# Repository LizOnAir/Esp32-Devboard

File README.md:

# ESP32 Devboard

This devboard is created to learn about PCB design rules. I plan to use PCBA for this board.

## Features:
-  battery charging
-  2.4GHz wifi
-  bluetooth

## PCB
Here's my PCB! It was made in KiCad. 
### Schematic

### PCB

## BOM:
Here should be [everything](https://docs.google.com/spreadsheets/d/1wsxLwNynfaC6R5-2-ovum9rVKD0-UjsQx3AUx7Wjfbc/edit?usp=sharing) you need to make this:
- 1x PCBA

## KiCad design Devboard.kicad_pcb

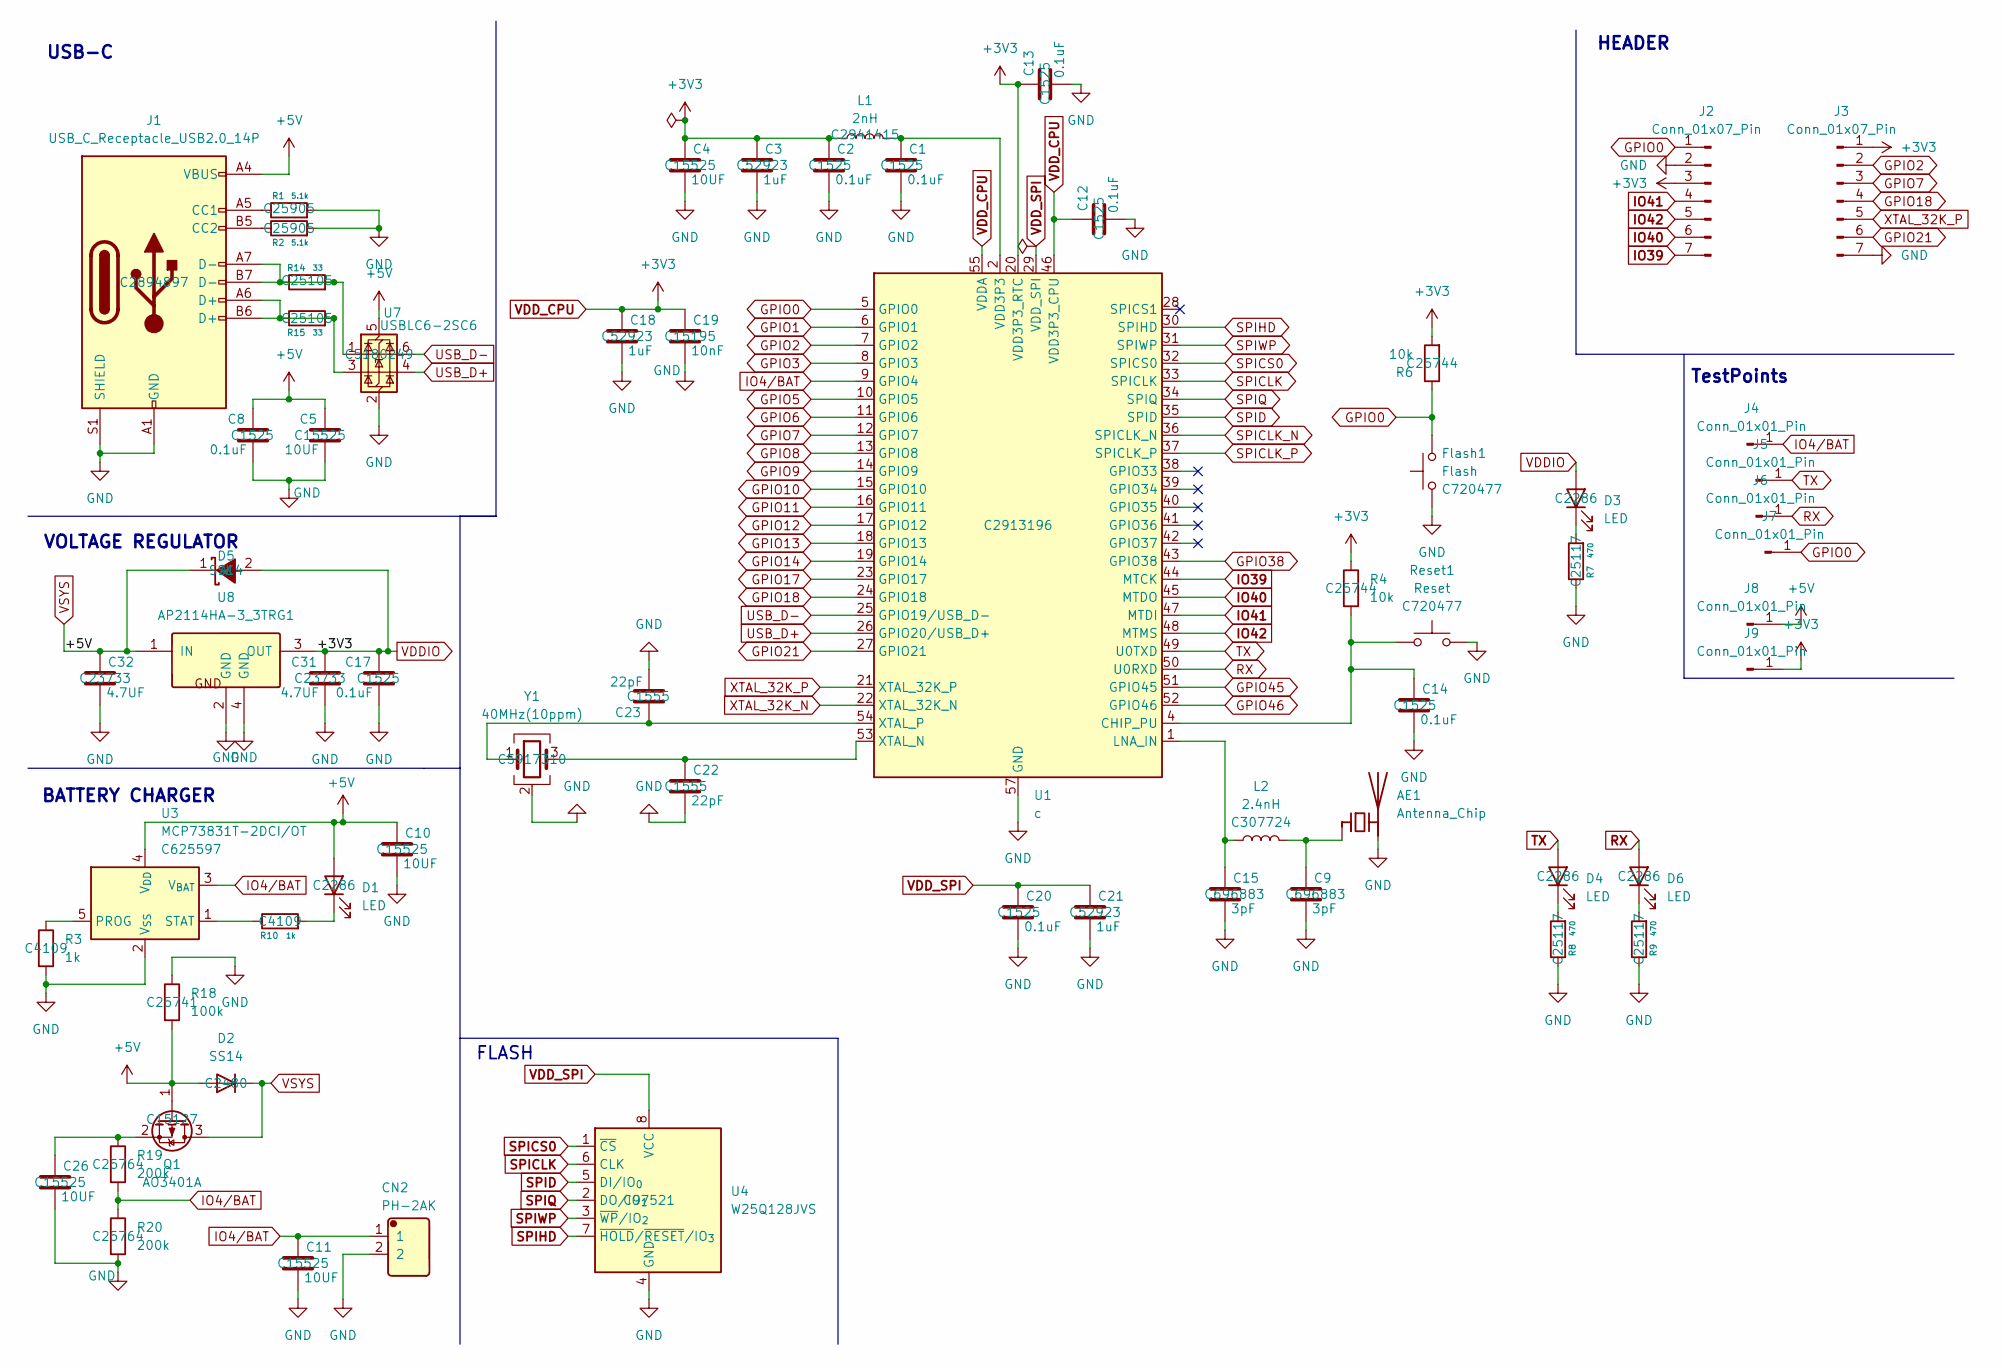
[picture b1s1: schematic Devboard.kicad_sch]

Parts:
AE1: Antenna_Chip; Texas_SWRA117D_2.4GHz_Left
C1, C2, C8, C12, C13, C14, C17, C20: 0.1uF; C_0402_1005Metric; MNF part num C1525
C3, C18, C21: 1uF; C_0402_1005Metric; MNF part num C52923
C4, C5, C10, C11, C26: 10UF; C_0402_1005Metric; MNF part num C15525
C9, C15: 3pF; C_0402_1005Metric; MNF part num C696883
C19: 10nF; C_0402_1005Metric; MNF part num C15195
C22, C23: 22pF; C_0402_1005Metric; MNF part num C1555
C31, C32: 4.7UF; C_0402_1005Metric; MNF part num C23733
CN2: PH-2AK; JST_PH_S2B-PH-K_1x02_P2.00mm_Horizontal; Manufacturer Part PH-2AK; LCSC C8886
D1, D3, D4, D6: LED; LED_0603_1608Metric; MNF part num C2286
D2: SS14; D_SMA; MNF part num C2480
D5: SS14; Manufacturer Part SS14; LCSC C2480
Flash1: Flash; SW_TS-1088-AR02016; MNF part num C720477
J1: USB_C_Receptacle_USB2.0_14P; USB_C_Receptacle_HCTL_HC-TYPE-C-16P-01A; MNF part num C2894897
J2, J3: Conn_01x07_Pin; PinHeader_1x07_P1.00mm_Vertical
J4, J5, J6, J7, J8, J9: Conn_01x01_Pin; TestPoint_Pad_D1.0mm
L1: 2nH; L_0402_1005Metric_Pad0.77x0.64mm_HandSolder; MNF part num C2941415
L2: 2.4nH; L_0402; MNF part num C307724
Q1: AO3401A; SOT-23; MNF part num C15127
R1, R2: 5.1k; R_0402; MNF part num C25905
R3, R10: 1k; R_0402; MNF part num C4109
R4, R6: 10k; R_0402_1005Metric; MNF part num C25744
R7, R8, R9: 470; R_0402; MNF part num C25117
R14, R15: 33; R_0402; MNF part num C25105
R18: 100k; R_0402; MNF part num C25741
R19, R20: 200k; R_0402; MNF part num C25764
Reset1: Reset; SW_TS-1088-AR02016; MNF part num C720477
U1: c; QFN-56-1EP_7x7mm_P0.4mm_EP4x4mm; MNF part num C2913196
U3: MCP73831T-2DCI/OT; SOT-23-5; MNF part num C625597
U4: W25Q128JVS; SOIC-8_5.3x5.3mm_P1.27mm; MNF part num C97521
U7: USBLC6-2SC6; SOT-23-6; MNF part num C5180249
U8: AP2114HA-3_3TRG1; Manufacturer Part AP2114HA-3.3TRG1; LCSC C460314
Y1: 40MHz(10ppm); Crystal_SMD_2520-4Pin_2.5x2.0mm; MNF part num C5917310

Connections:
GND: AE1.2 (PCB_Trace), C1.2, C2.2, C3.2, C4.2, C5.2, C8.2, C9.2, C10.2, C11.2, C12.2, C13.2, C14.2, C15.2, C17.2, C18.2, C19.2, C20.2, C21.2, C22.2, C23.2, C26.2, C31.2, C32.2, CN2.2, Flash1.1, J1.A1 (GND), J1.A12 (GND), J1.B1 (GND), J1.B12 (GND), J1.S1 (SHIELD), J2.2, J3.7, R1.2, R2.2, R3.2, R7.1, R8.1, R9.1, R18.1, R20.2, Reset1.2, U1.57 (GND), U3.2 (V_{SS}), U4.4 (GND), U7.2 (GND), U8.2 (GND), U8.4 (GND), Y1.2 (G), Y1.4 (G)
GPIO0: Flash1.2, J2.1, J7.1, R6.1, U1.5 (GPIO0)
GPIO1: U1.6 (GPIO1)
GPIO2: J3.2, U1.7 (GPIO2)
GPIO3: U1.8 (GPIO3)
GPIO5: U1.10 (GPIO5)
GPIO6: U1.11 (GPIO6)
GPIO7: J3.3, U1.12 (GPIO7)
GPIO8: U1.13 (GPIO8)
GPIO9: U1.14 (GPIO9)
GPIO10: U1.15 (GPIO10)
GPIO11: U1.16 (GPIO11)
GPIO12: U1.17 (GPIO12)
GPIO13: U1.18 (GPIO13)
GPIO14: U1.19 (GPIO14)
GPIO17: U1.23 (GPIO17)
GPIO18: J3.4, U1.24 (GPIO18)
GPIO21: J3.6, U1.27 (GPIO21)
GPIO38: U1.43 (GPIO38)
GPIO45: U1.51 (GPIO45)
GPIO46: U1.52 (GPIO46)
IO4/BAT: C11.1, CN2.1, J4.1, R19.2, R20.1, U1.9 (GPIO4), U3.3 (V_{BAT})
IO39: J2.7, U1.44 (MTCK)
IO40: J2.6, U1.45 (MTDO)
IO41: J2.4, U1.47 (MTDI)
IO42: J2.5, U1.48 (MTMS)
unnamed: AE1.1 (FEED), C9.1, L2.2
unnamed: C1.1, L1.2, U1.2 (VDD3P3), U1.3 (VDD3P3)
unnamed: D1.1 (K), R10.2
unnamed: D3.1 (K), R7.2
unnamed: D4.1 (K), R8.2
unnamed: D6.1 (K), R9.2
unnamed: J1.A5 (CC1), R1.1
unnamed: J1.B5 (CC2), R2.1
unnamed: J1.A6 (D+), J1.B6 (D+), R15.1, R15.2, U7.3 (I/O2)
unnamed: J1.A7 (D-), J1.B7 (D-), R14.1, R14.2, U7.1 (I/O1)
unnamed: C26.1, Q1.2 (S), R19.1
unnamed: C14.1, R4.2, Reset1.1, U1.4 (CHIP_PU)
unnamed: C15.1, L2.1, U1.1 (LNA_IN)
unnamed: C22.1, U1.53 (XTAL_N), Y1.3
unnamed: C23.1, U1.54 (XTAL_P), Y1.1
unnamed: R3.1, U3.5 (PROG)
unnamed: R10.1, U3.1 (STAT)
RX: D6.2 (A), J6.1, U1.50 (U0RXD)
SPICLK: U1.33 (SPICLK), U4.6 (CLK)
SPICLK_N: U1.36 (SPICLK_N)
SPICLK_P: U1.37 (SPICLK_P)
SPICS0: U1.32 (SPICS0), U4.1 (~CS)
SPID: U1.35 (SPID), U4.5 (DI/IO_{0})
SPIHD: U1.30 (SPIHD), U4.7 (~HOLD/~RESET/IO_{3})
SPIQ: U1.34 (SPIQ), U4.2 (DO/IO_{1})
SPIWP: U1.31 (SPIWP), U4.3 (~WP/IO_{2})
TX: D4.2 (A), J5.1, U1.49 (U0TXD)
USB_D+: U1.26 (GPIO20/USB_D+), U7.4 (I/O2)
USB_D-: U1.25 (GPIO19/USB_D-), U7.6 (I/O1)
VDDIO: C2.1, C3.1, C4.1, C12.1, C13.1, C17.1, C18.1, C19.1, C31.1, D3.2 (A), D5.2 (A), J2.3, J3.1, J9.1, L1.1, R4.1, R6.2, U1.20 (VDD3P3_RTC), U1.46 (VDD3P3_CPU), U1.55 (VDDA), U1.56 (VDDA), U8.3 (OUT)
VDD_SPI: C20.1, C21.1, U1.29 (VDD_SPI), U4.8 (VCC)
VSYS: C5.1, C8.1, C10.1, C32.1, D1.2 (A), D2.1 (K), D2.2 (A), D5.1 (K), J1.A4 (VBUS), J1.A9 (VBUS), J1.B4 (VBUS), J1.B9 (VBUS), J8.1, Q1.1 (G), Q1.3 (D), R18.2, U3.4 (V_{DD}), U7.5 (VBUS), U8.1 (IN)
XTAL_32K_N: U1.22 (XTAL_32K_N)
XTAL_32K_P: J3.5, U1.21 (XTAL_32K_P)

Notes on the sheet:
FLASH
BATTERY CHARGER
HEADER
VOLTAGE REGULATOR
USB-C
TestPoints

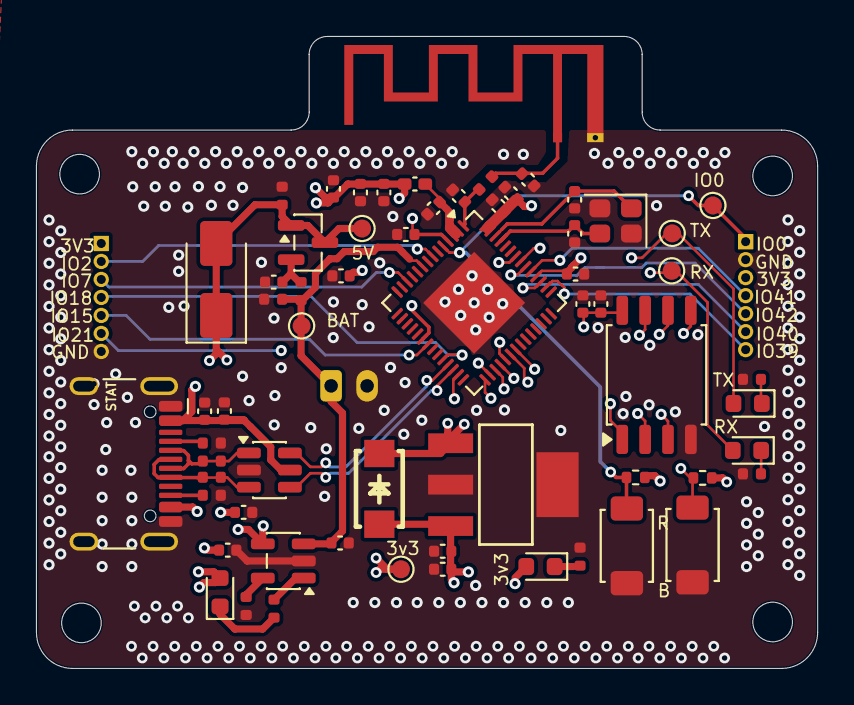
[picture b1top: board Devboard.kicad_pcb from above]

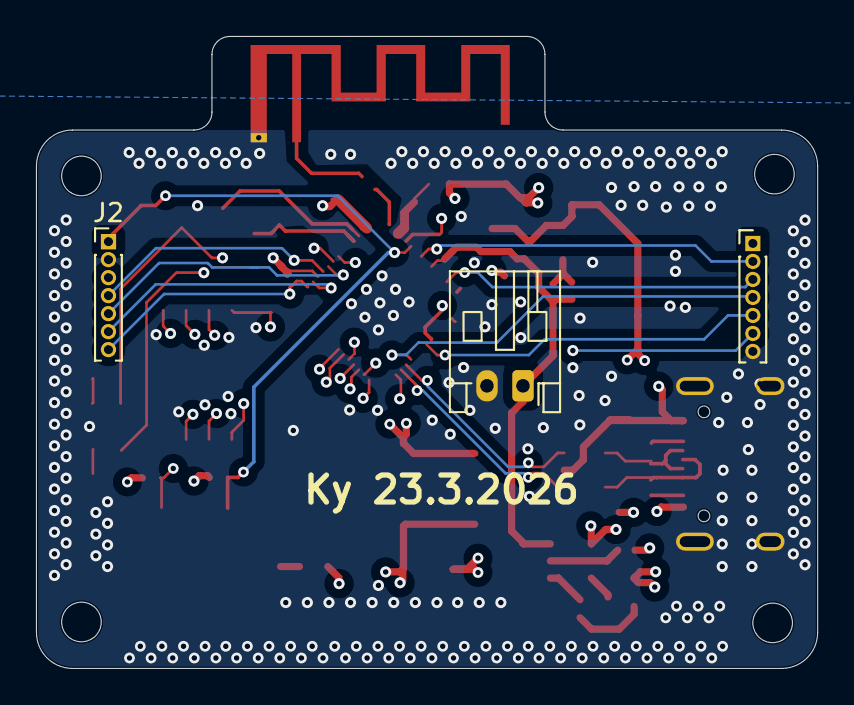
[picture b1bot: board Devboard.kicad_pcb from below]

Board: 4 copper layers, 43.4 x 35.1 mm, 65 parts (3 on the bottom side), 42 nets.

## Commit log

2026-04-14 Rename Devboard.kicad_pcb to PCB/Devboard.kicad_pcb
2026-04-14 Rename Devboard.kicad_pro to PCB/Devboard.kicad_pro
2026-04-14 Rename Devboard.zip to PCB/Devboard.zip
2026-04-14 Rename Devboard.kicad_prl to PCB/Devboard.kicad_prl
2026-04-14 Rename Devboard.kicad_sch to PCB/Devboard.kicad_sch
2026-04-14 Create README.md for ESP32 Devboard project
    Added a README file with project details and features.
